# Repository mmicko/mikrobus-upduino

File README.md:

# mikrobus-upduino
Dual MikroBUS board for Upduino 2 FPGA

**NOTE**
Hardware version 0.1 is not production ready. Please do not fabricate.

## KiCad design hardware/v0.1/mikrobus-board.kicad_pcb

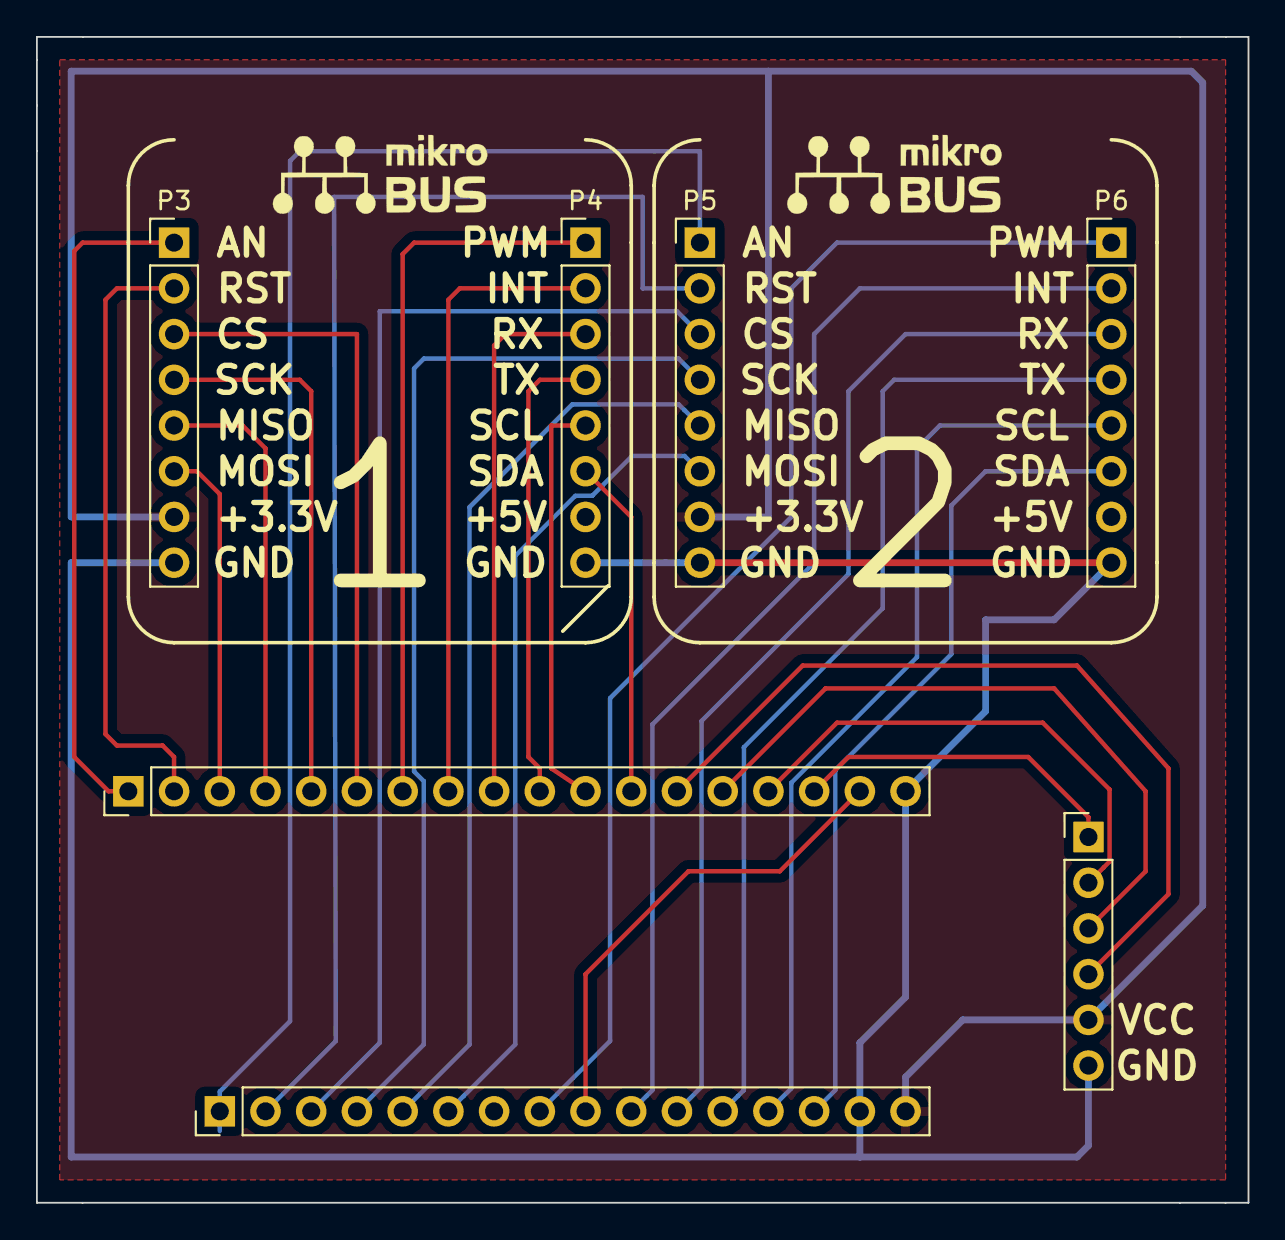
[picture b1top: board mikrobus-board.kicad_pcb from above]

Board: 2 copper layers, 67.3 x 64.8 mm, 9 parts (0 on the bottom side), 31 nets.

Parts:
G1, G1#2: LOGO; mikrobus
J1: Conn_01x06; Pin_Header_Straight_1x06_Pitch2.54mm
P3, P5: microBus_1; Socket_Strip_Straight_1x08_Pitch2.54mm
P4, P6: microBus_2; Socket_Strip_Straight_1x08_Pitch2.54mm
UP1: Conn_01x18; Socket_Strip_Straight_1x18_Pitch2.54mm
UPDUINO2_DOWN1: Conn_01x16; Socket_Strip_Straight_1x16_Pitch2.54mm

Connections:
+3V3: J1.5, P3.7, P5.7, UPDUINO2_DOWN1.16
/AN_1: P3.1, UP1.1
/AN_2: P5.1, UPDUINO2_DOWN1.1
/CS_1: P3.3, UP1.6
/CS_2: P5.3, UPDUINO2_DOWN1.3
/EXT_1: J1.4, UP1.13
/EXT_2: J1.3, UP1.14
/EXT_3: J1.2, UP1.15
/EXT_4: J1.1, UP1.16
/INT_1: P4.2, UP1.8
/INT_2: P6.2, UPDUINO2_DOWN1.10
/MISO_1: P3.5, UP1.4
/MISO_2: P5.5, UPDUINO2_DOWN1.5
/MOSI_1: P3.6, UP1.3
/MOSI_2: P5.6, UPDUINO2_DOWN1.6
/OSC_OUT: UP1.17, UPDUINO2_DOWN1.9
/PWM_1: P4.1, UP1.7
/PWM_2: P6.1, UPDUINO2_DOWN1.8
/RST_1: P3.2, UP1.2
/RST_2: P5.2, UPDUINO2_DOWN1.2
/RX_1: P4.3, UP1.9
/RX_2: P6.3, UPDUINO2_DOWN1.11
/SCK_1: P3.4, UP1.5
/SCK_2: P5.4, UPDUINO2_DOWN1.4
/SCL_1: P4.5, UP1.11
/SCL_2: P6.5, UPDUINO2_DOWN1.13
/SDA_1: P4.6, UP1.12
/SDA_2: P6.6, UPDUINO2_DOWN1.14
/TX_1: P4.4, UP1.10
/TX_2: P6.4, UPDUINO2_DOWN1.12
GND: J1.6, P3.8, P4.8, P5.8, P6.8, UP1.18, UPDUINO2_DOWN1.15

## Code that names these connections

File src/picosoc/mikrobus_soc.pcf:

# TODO: pcf

set_io -nowarn flash_csb 16
set_io -nowarn flash_clk 15
set_io -nowarn flash_io0 14
set_io -nowarn flash_io1 17

# TODO : QSPI
set_io -nowarn flash_io2 31
set_io -nowarn flash_io3 34

set_io -nowarn RGB0 39
set_io -nowarn RGB1 40
set_io -nowarn RGB2 41

set_io -nowarn AN_1    12
set_io -nowarn RST_1   21
set_io -nowarn MOSI_1  13
set_io -nowarn MISO_1  19
set_io -nowarn SCK_1   18
set_io -nowarn CS_1    11
set_io -nowarn PWM_1    9
set_io -nowarn INT_1    6
set_io -nowarn RX_1    44
set_io -nowarn TX_1     4
set_io -nowarn SCL_1    3
set_io -nowarn SDA_1   48
set_io -nowarn ser_tx  45 # set_io EXT_1   45
set_io -nowarn ser_rx  47 # set_io EXT_2   47
set_io -nowarn EXT_3   46
set_io -nowarn EXT_4    2

set_io -nowarn AN_2    23
set_io -nowarn RST_2   25
set_io -nowarn CS_2    26
set_io -nowarn SCK_2   27
set_io -nowarn MISO_2  32
set_io -nowarn MOSI_2  35
#set_io -nowarn NC_1    31
set_io -nowarn PWM_2   37
#set_io -nowarn NC_2    34
set_io -nowarn INT_2   43
set_io -nowarn RX_2    35
set_io -nowarn TX_2    42
set_io -nowarn SCL_2   38
set_io -nowarn SDA_2   28

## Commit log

2018-05-17 Prototype version
2018-05-17 Added some example of usage MikroBUS devices
2018-05-19 Added 2nd I2C
2018-05-19 Added support for more GPIO
2018-05-20 more demos
2018-05-24 Fix Makefile
